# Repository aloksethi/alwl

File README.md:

# alwl
continuation of fabacademy project --> not anymore
Details will be at https://aloksethi.netlify.com/project/fablabfinal/

This project took a lot of different turns. Below mentioned is the current status

* Not a desk lamp anymore 
* Installed a SK6812 LED strip in the room and controlling it with an IR remote control
* Power is coming from an old laptop adapter. Have used a buck converter module to convert it to 5V

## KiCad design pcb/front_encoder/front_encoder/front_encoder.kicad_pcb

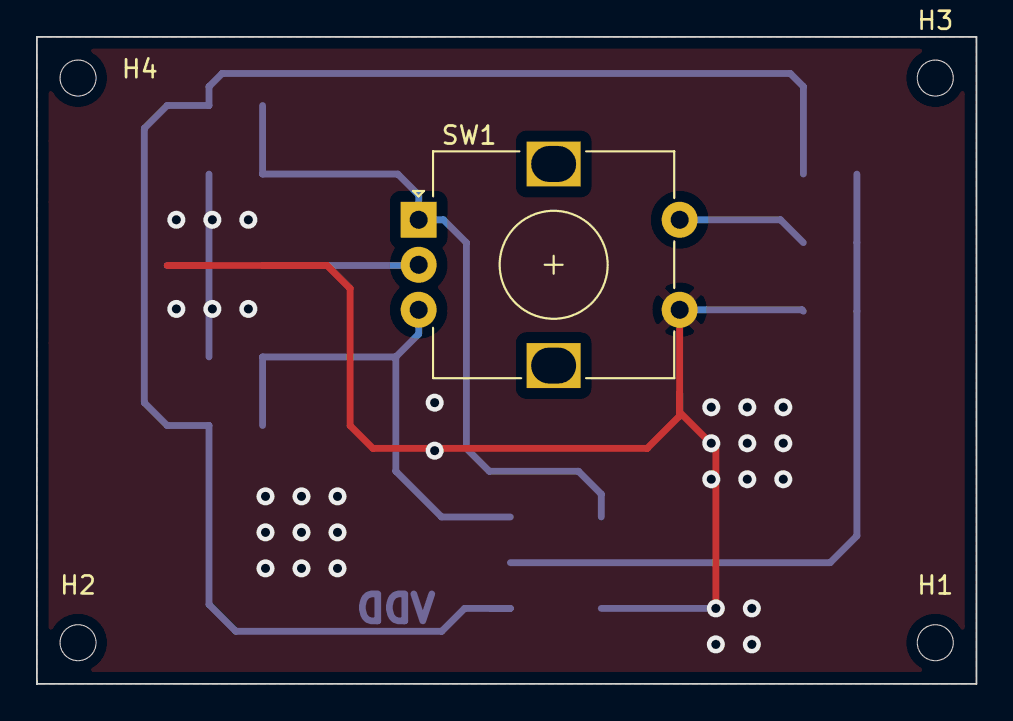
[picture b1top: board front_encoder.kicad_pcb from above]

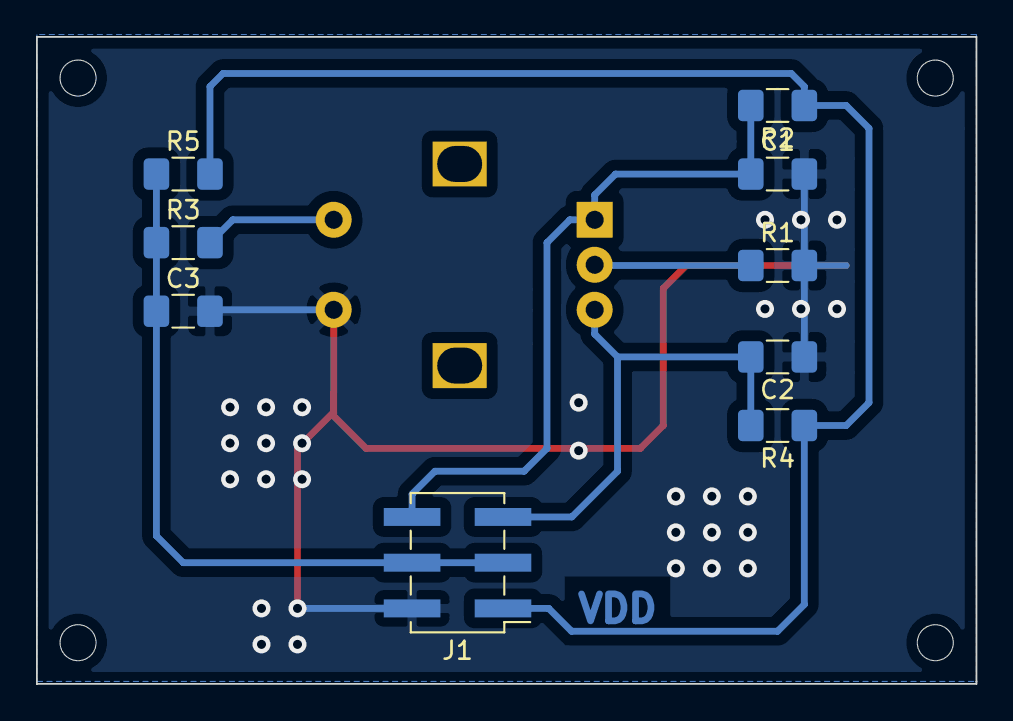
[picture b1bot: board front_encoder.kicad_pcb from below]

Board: 2 copper layers, 52.2 x 35.9 mm, 14 parts (9 on the bottom side), 7 nets.

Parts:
C1, C2, C3: 1u; C_1206_3216Metric_Pad1.42x1.75mm_HandSolder
H1, H2, H3, H4: MountingHole; MountingHole_2mm
J1: Conn_02x03_Top_Bottom; PinHeader_2x03_P2.54mm_Vertical_SMD
R1, R3: 100; R_1206_3216Metric_Pad1.42x1.75mm_HandSolder
R2, R5: 10K; R_1206_3216Metric_Pad1.42x1.75mm_HandSolder
R4: 20K; R_1206_3216Metric_Pad1.42x1.75mm_HandSolder
SW1: Rotary_Encoder_Switch; RotaryEncoder_Alps_EC12E-Switch_Vertical_H20mm

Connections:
GND: C1.2, C2.1, C3.2, J1.2, R1.2, SW1.S2
unnamed: C1.1, J1.6, R2.2, SW1.A
unnamed: C2.2, J1.5, R4.2, SW1.B
unnamed: C3.1, J1.3, J1.4, R3.1, R5.1
unnamed: R1.1, SW1.C
unnamed: R3.2, SW1.S1
VDD: J1.1, R2.1, R4.1, R5.2

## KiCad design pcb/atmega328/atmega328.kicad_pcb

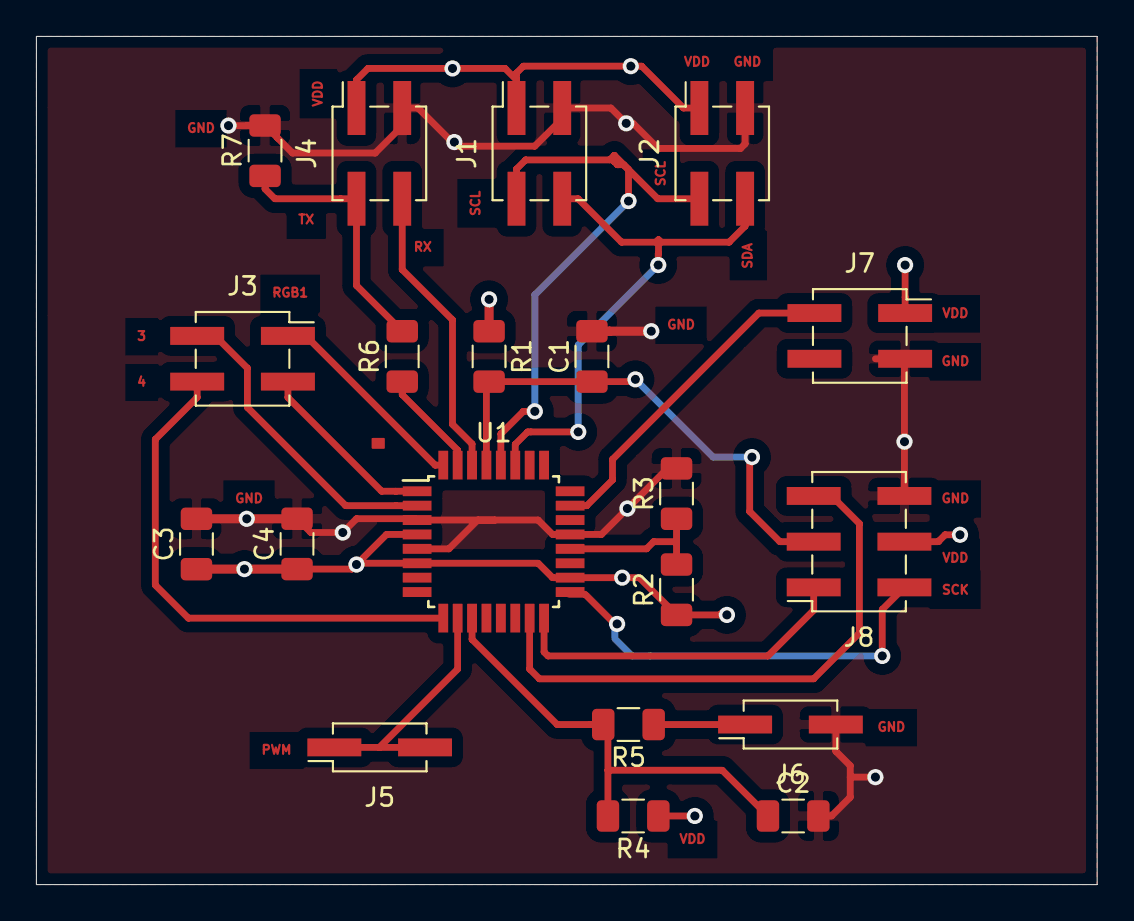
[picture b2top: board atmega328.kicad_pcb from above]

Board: 4 copper layers, 58.9 x 47.1 mm, 20 parts (0 on the bottom side), 20 nets.

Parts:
C1, C2: 1uF; C_1206_3216Metric
C3: 100nF; C_1206_3216Metric
C4: 10nF; C_1206_3216Metric
J1: Conn_I2C_DISPLAY; PinSocket_2x02_P2.54mm_Vertical_SMD
J2: Conn_I2C_RTC; PinSocket_2x02_P2.54mm_Vertical_SMD
J3: Conn_RGB_Ctrl; PinSocket_2x02_P2.54mm_Vertical_SMD
J4: Conn_bluetooth; PinSocket_2x02_P2.54mm_Vertical_SMD
J5: Conn_pwm_wled; PinSocket_2x01_P2.54mm_Vertical_SMD
J6: Conn_fpanel_swtch; PinSocket_2x01_P2.54mm_Vertical_SMD
J7: Conn_light_sensor; PinSocket_2x02_P2.54mm_Vertical_SMD
J8: Conn_ISP; PinSocket_2x03_P2.54mm_Vertical_SMD
R1, R2, R3, R5: 10K; R_1206_3216Metric
R4: 20K; R_1206_3216Metric
R6: 1K; R_1206_3216Metric
R7: 2K; R_1206_3216Metric
U1: ATmega328P-AU; TQFP-32_7x7mm_P0.8mm

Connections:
/AIP: J7.2, U1.23
/MISO: J8.1, U1.16
/MOSI: J8.5, U1.15
/PWM: J5.1, J5.2, U1.10
/RGB1: J3.1, U1.32
/RGB2: J3.3, U1.1
/RGB3: J3.2, U1.2
/RGB4: J3.4, U1.9
/RST: C1.1, J8.3, R1.2, U1.29
/SCK: J8.2, U1.17
/SCL: J1.2, J2.2, U1.28
/SDA: J1.4, J2.4, U1.27
/SRX: J4.4, U1.30
/STX: J4.2, R6.2, R7.1
/SW_DB: J6.1, R5.1
GND: C1.2, C2.2, C3.2, C4.2, J1.3, J2.3, J4.3, J6.2, J7.3, J8.6, R3.2, R7.2, U1.3, U1.5, U1.21
unnamed: C2.1, R4.2, R5.2, U1.11
unnamed: R2.2, R3.1, U1.20
unnamed: R6.1, U1.31
VDD: C3.1, C4.1, J1.1, J2.1, J4.1, J7.1, J8.4, R1.1, R2.1, R4.1, U1.4, U1.6, U1.18

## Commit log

2019-11-23 first version of the pcb with ATmega328P
2020-02-21 added extensions for kicad backup files
2020-02-21 initial source code. handles infrared and the LED strip
2020-02-21 pcbs for a rotary encoder
2020-02-21 updated the readme
